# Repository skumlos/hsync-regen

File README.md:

HSYNC Re-generation circuit

This circuit is based on (and very close to being a 100% copy of) Renesas Technical Brief 476
(tb476) associated with the ISL59885 sync-separator IC.

The basic idea is that some sync signals (looking at you SEGA Master System) do not adhere to
"proper" sync waveform, mainly meaning that during VSYNC, HSYNC is completely missing. This
will usually show itself as a "skew" in the top (or even more) of the video image, as the PLL
circuit of the monitor loses lock to the horizontal sync, and has to re-acquire it after each
vertical sync. To avoid this, creating a re-generated horizontal sync signal, derived from
the original, but ever-present, is the key. This circuit does this completely through discrete
components, and at the same time allows for HVSYNC, as the ISL59885 outputs both HSYNC and
VSYNC as separate signals. Should work for both CSYNC and Sync-on-Green (Y of YPbPr) signals
(latter untested).

This should be especially useful for monitors that show (excessive) flagging (like Sony BVM-A,
BVM D9/D14 or JVC DT-V monitors).

Jumper descriptions (looking at component side, BNC outputs to right):

JP2 Input is 75 Ohm terminated (down) or not (up).

JP3 Source signal is passed directly to the output (up) or the sync stripped version (down).

JP4 HSYNC output is HSYNC (right) or CSYNC (including the regenerated HSYNC) (left).

For a complete description, read the technical brief, which is available on Renesas' website
under "Documents" section for the ISL59885.

Attach CSYNC (or Y/G) to the input, and connect HSYNC and VSYNC to monitor (or JP4 set to CSYNC
and then HSYNC (now CSYNC) to monitor sync input). Board needs to powered by 5V from USB or
through J6.

(2020) Martin Hejnfelt (martin@hejnfelt.com)

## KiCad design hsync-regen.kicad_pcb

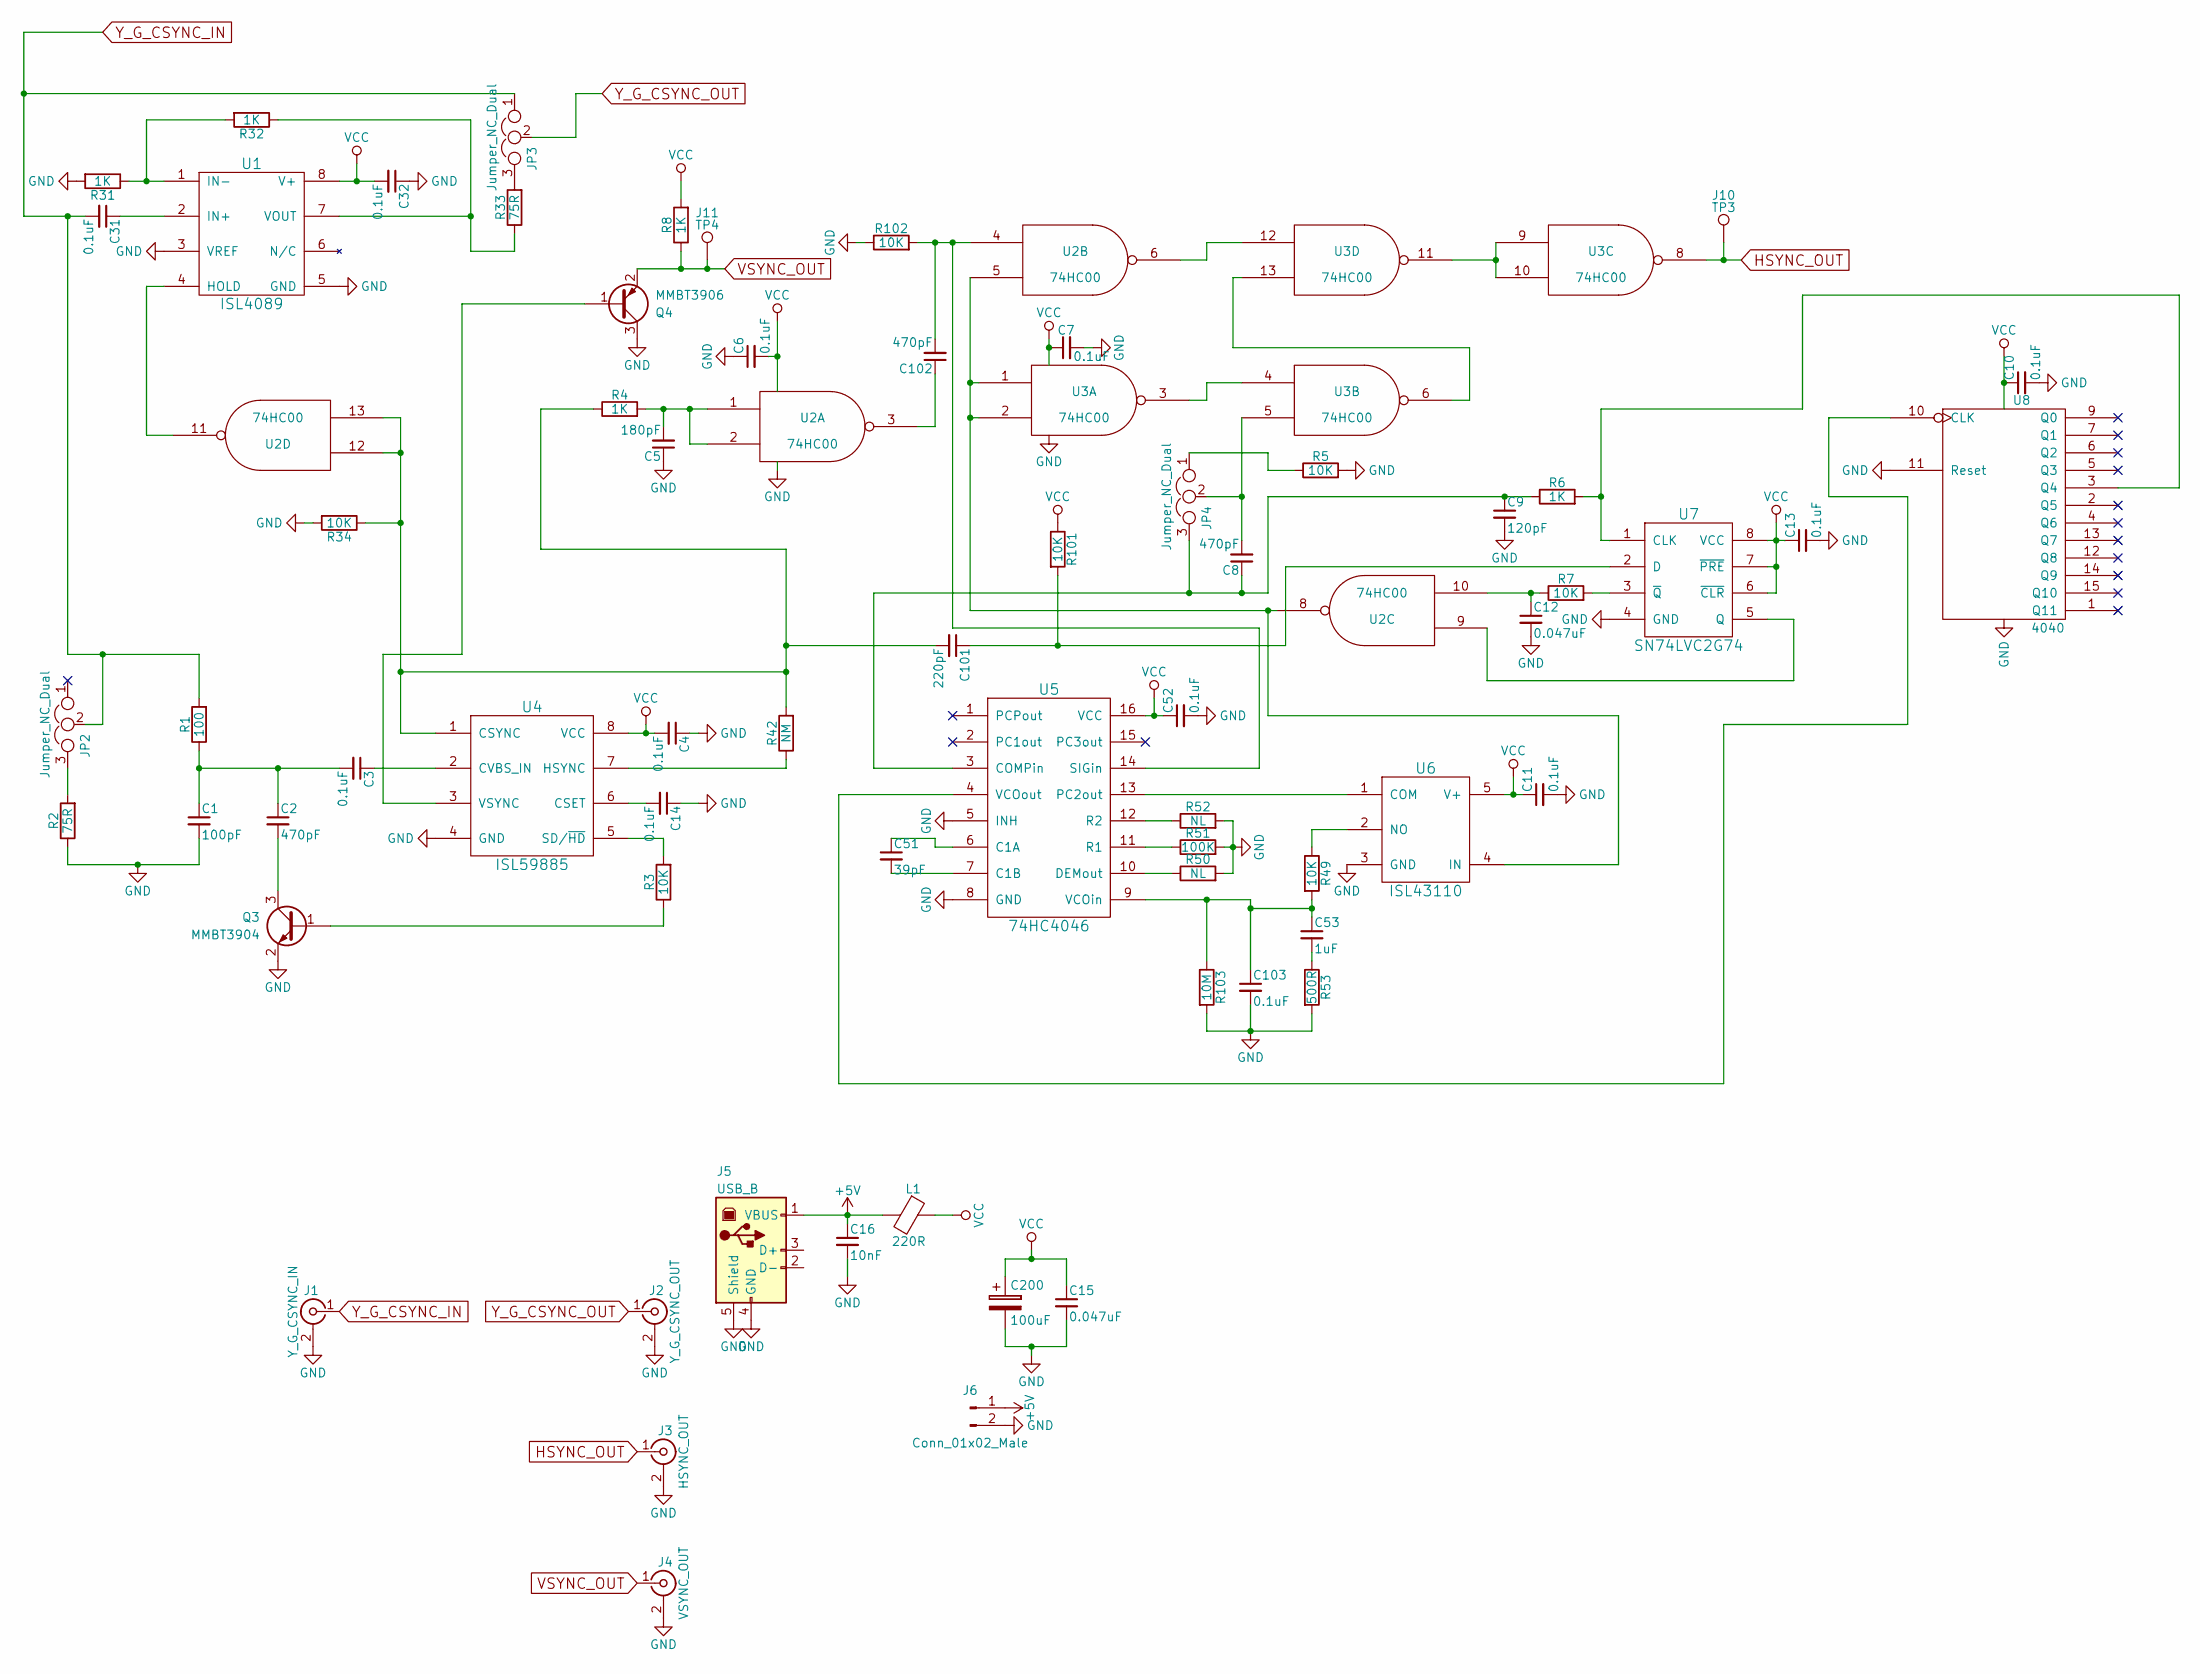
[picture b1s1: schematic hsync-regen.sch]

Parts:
C1: 100pF; C_0805_HandSoldering
C2, C8, C102: 470pF; C_0805_HandSoldering
C3, C4, C6, C7, C10, C11, C13, C14, C31, C32, C52, C103: 0.1uF; C_0805_HandSoldering
C5: 180pF; C_0805_HandSoldering
C9: 120pF; C_0805_HandSoldering
C12, C15: 0.047uF; C_0805_HandSoldering
C16: 10nF; C_0805_HandSoldering
C51: 39pF; C_0805_HandSoldering
C53: 1uF; C_0805_HandSoldering
C101: 220pF; C_0805_HandSoldering
C200: 100uF; CP_Elec_6.3x5.3
J1: Y_G_CSYNC_IN; BNC-THT
J2: Y_G_CSYNC_OUT; BNC-THT
J3: HSYNC_OUT; BNC-THT
J4: VSYNC_OUT; BNC-THT
J5: USB_B; USB_Micro-B
J6: Conn_01x02_Male; Pin_Header_Straight_1x02_Pitch2.54mm
J10: TP3; Measurement_Point_Round-SMD-Pad_Big
J11: TP4; Measurement_Point_Round-SMD-Pad_Big
JP2, JP3, JP4: Jumper_NC_Dual; Pin_Header_Straight_1x03_Pitch2.54mm
L1: 220R; R_0805_HandSoldering
Q3: MMBT3904; SOT-23_Handsoldering
Q4: MMBT3906; SOT-23_Handsoldering
R1: 100; R_0805_HandSoldering
R2, R33: 75R; R_0805_HandSoldering
R3, R5, R7, R34, R49, R101, R102: 10K; R_0805_HandSoldering
R4, R6, R8, R31, R32: 1K; R_0805_HandSoldering
R42: NM; R_0805_HandSoldering
R50, R52: NL; R_0805_HandSoldering
R51: 100K; R_0805_HandSoldering
R53: 500R; R_0805_HandSoldering
R103: 10M; R_0805_HandSoldering
U1: ISL4089; SOIC-8_3.9x4.9mm_Pitch1.27mm
U2, U3: 74HC00; TSSOP-14_4.4x5mm_Pitch0.65mm
U4: ISL59885; SOIC-8_3.9x4.9mm_Pitch1.27mm
U5: 74HC4046; TSSOP-16_4.4x5mm_Pitch0.65mm
U6: ISL43110; SOT-23-5
U7: SN74LVC2G74; VSSOP-8_2.3x2mm_Pitch0.5mm
U8: 4040; TSSOP-16_4.4x5mm_Pitch0.65mm

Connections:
+5V: C16.1, J5.1 (VBUS), J6.1, L1.2
GND: C1.2, C4.1, C5.1, C6.1, C7.2, C9.2, C10.2, C11.2, C12.2, C13.2, C14.1, C15.2, C16.2, C32.1, C52.2, C103.2, C200.2, J1.2 (Ext), J2.2 (Ext), J3.2 (Ext), J4.2 (Ext), J5.4 (GND), J5.5 (Shield), J6.2, Q3.2 (E), Q4.3 (C), R2.1, R5.2, R31.2, R34.2, R50.2, R51.2, R52.2, R53.2, R102.1, R103.2, U1.3 (VREF), U1.5 (GND), U2.7 (GND), U3.7 (GND), U4.4 (GND), U5.5 (INH), U5.8 (GND), U6.3 (GND), U7.4 (GND), U8.8 (VSS), U8.11 (Reset)
HSYNC_OUT: J3.1 (In), J10.1, U3.8
unnamed: C1.1, C2.1, C3.2, R1.1
unnamed: C2.2, Q3.3 (C)
unnamed: C3.1, U4.2 (CVBS_IN)
unnamed: C5.2, R4.2, U2.1, U2.2
unnamed: C8.1, C9.1, JP4.3, R6.1, U5.3 (COMPin)
unnamed: C8.2, JP4.2, U3.5
unnamed: C12.1, R7.1, U2.10
unnamed: C14.2, U4.6 (CSET)
unnamed: C31.1, U1.2 (IN+)
unnamed: C51.1, U5.6 (C1A)
unnamed: C51.2, U5.7 (C1B)
unnamed: C53.2, R53.1
unnamed: C101.1, R101.2, U7.2 (D)
unnamed: C101.2, R4.1, R34.1, R42.2, U2.12, U2.13, U4.1 (CSYNC)
unnamed: C102.1, U2.3
unnamed: C102.2, R102.2, U2.4, U5.14 (SIGin)
unnamed: C53.1, C103.1, R49.2, R103.1, U5.9 (VCOin)
unnamed: JP2.3, R2.2
unnamed: JP3.3, R33.2
unnamed: JP4.1, R5.1
unnamed: Q3.1 (B), R3.1
unnamed: Q4.1 (B), U4.3 (VSYNC)
unnamed: R3.2, U4.5 (SD/~HD)
unnamed: R6.2, U7.1 (CLK), U8.3 (Q4)
unnamed: R7.2, U7.3 (~Q)
unnamed: R31.1, R32.2, U1.1 (IN-)
unnamed: R32.1, R33.1, U1.7 (VOUT)
unnamed: R42.1, U4.7 (HSYNC)
unnamed: R49.1, U6.2 (NO)
unnamed: R50.1, U5.10 (DEMout)
unnamed: R51.1, U5.11 (R1)
unnamed: R52.1, U5.12 (R2)
unnamed: U1.4 (HOLD), U2.11
unnamed: U2.5, U2.8, U3.1, U3.2, U6.4 (IN)
unnamed: U2.6, U3.12
unnamed: U2.9, U7.5 (Q)
unnamed: U3.3, U3.4
unnamed: U3.9, U3.10, U3.11
unnamed: U3.6, U3.13
unnamed: U5.4 (VCOout), U8.10 (CLK)
unnamed: U5.13 (PC2out), U6.1 (COM)
VCC: C4.2, C6.2, C7.1, C10.1, C11.1, C13.1, C15.1, C32.2, C52.1, C200.1, L1.1, R8.2, R101.1, U1.8 (V+), U2.14 (VCC), U3.14 (VCC), U4.8 (VCC), U5.16 (VCC), U6.5 (V+), U7.6 (~CLR), U7.7 (~PRE), U7.8 (VCC), U8.16 (VDD)
VSYNC_OUT: J4.1 (In), J11.1, Q4.2 (E), R8.1
Y_G_CSYNC_IN: C31.2, J1.1 (In), JP2.2, JP3.1, R1.2
Y_G_CSYNC_OUT: J2.1 (In), JP3.2

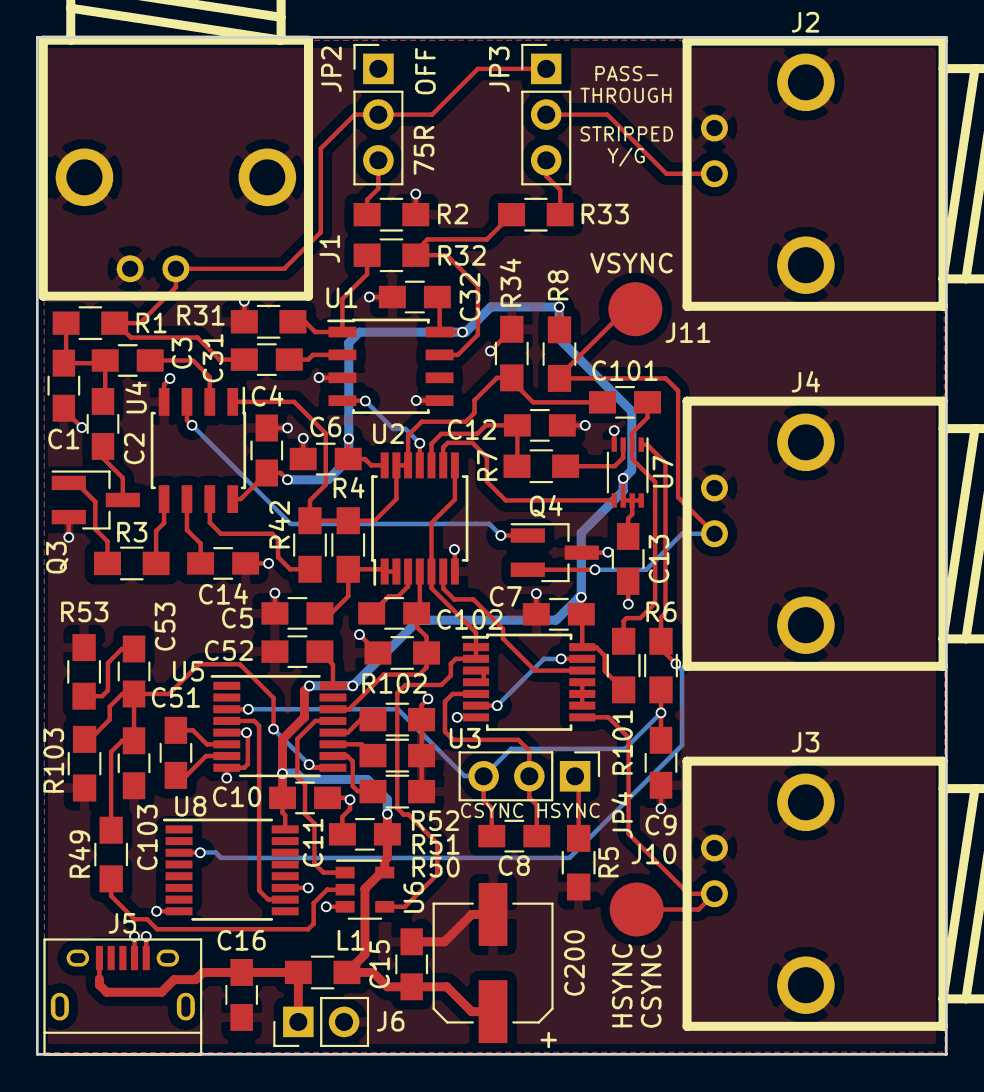
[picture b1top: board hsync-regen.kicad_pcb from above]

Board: 2 copper layers, 50.5 x 56.5 mm, 68 parts (0 on the bottom side), 48 nets.

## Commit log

2020-09-06 Minor README niceification
2020-11-14 Minor fixes and nicifications
